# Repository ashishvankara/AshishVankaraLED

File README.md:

# Ashish Vankara Prototyping Skills: Blinking Light Project

## Introduction
An LED light-blinking apparatus that switches between 5 different operating modes (shown below) was created.

    - off
    - brightest
    - Intermediate Brightness
    - Least Bright
    - Flashing at 2Hz
 
## Design Repository Description
This design repository is organized into the following directories:

    -Docs: contains datasheets, and initial circuit and software planning schematics
    -Electronics: contains the initial circuit diagrams
    -Hardware: contains the project's ECAD files
        - Final iteration: LEDproject.11.18.18.brd & LEDproject.11.18.18.sch
    -Mechanical: contains the project's CAD files
        - Final iteration: Bottom.Final.STL & Top.Final.STL
    -Software: contains the software flow chart as well as the arduino script utilized in this project

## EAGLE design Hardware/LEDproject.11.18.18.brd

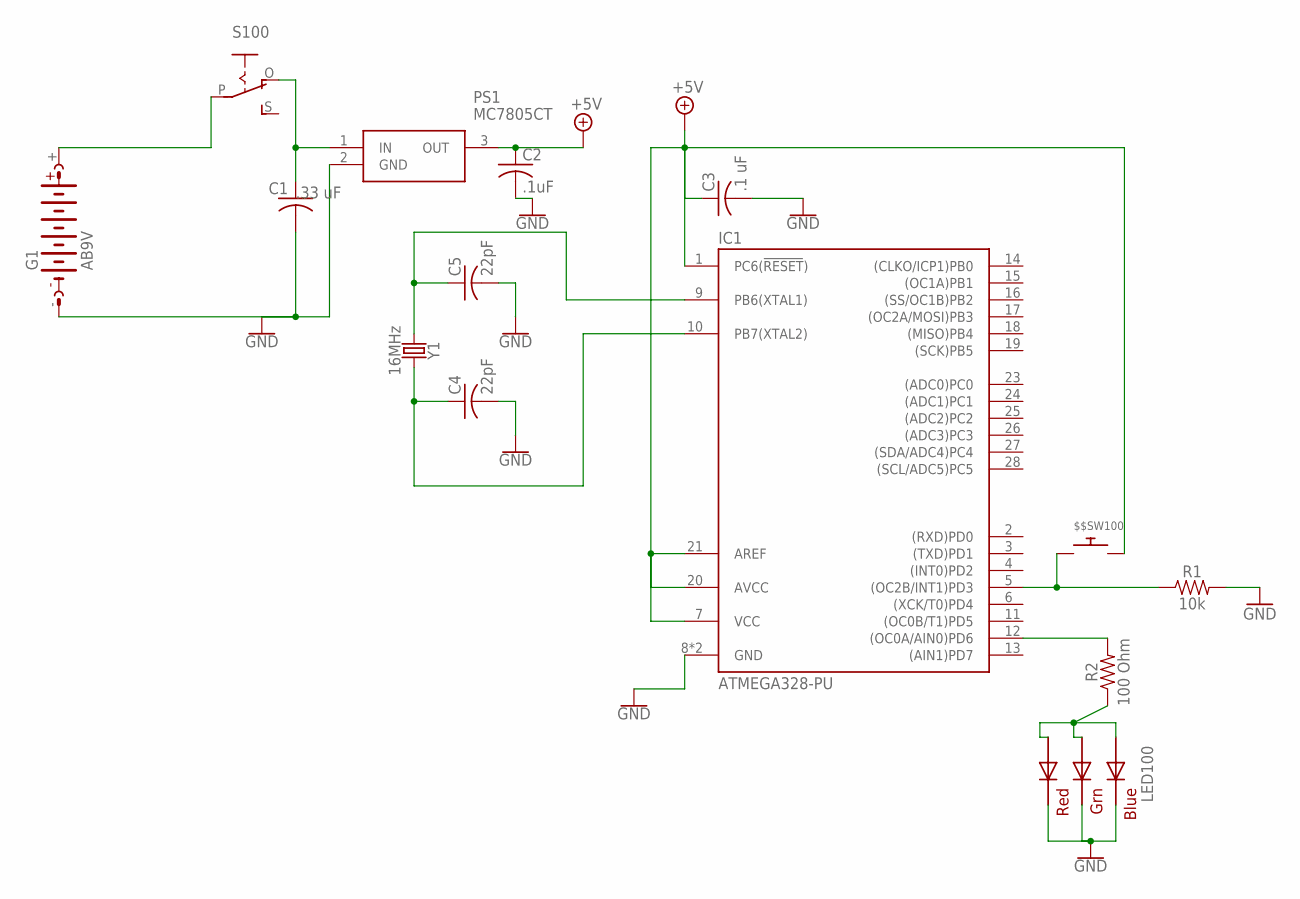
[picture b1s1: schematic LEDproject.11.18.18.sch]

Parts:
$$SW100: SWITCH_PUSHBUTTONEVQ-PE; TACT_PANA-EVQ
C1: C-US025-030X050; C025-030X050
C2: .1uF; C025-030X050
C3: .1 uF; C025-030X050
C4, C5: 22pF; C025-030X050
G1: AB9V
IC1: ATMEGA328-PU; DIL28
LED100: RGBLED5050
PS1: MC7805CT; TO254P482X997X1968-3P
R1: 10k; AXIAL-0.3
R2: 100 Ohm; AXIAL-0.3
S100: EG1218S; EG1218
Y1: 16MHz; HC49US

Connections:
+5V: $$SW100.P$2, C2.1, C3.1, IC1.1 (PC6(!RESET!)), IC1.7 (VCC), IC1.20 (AVCC), IC1.21 (AREF), PS1.3 (OUT)
GND: C1.2, C2.2, C3.2, C4.2, C5.2, G1.-, IC1.8 (GND), IC1.22 (GND), LED100.4 (BLUE_C), LED100.5 (RED_C), LED100.6 (GREEN_C), PS1.2 (GND), R1.P$2 (2)
unnamed: C5.1, IC1.9 (PB6(XTAL1)), Y1.1
unnamed: C4.1, IC1.10 (PB7(XTAL2)), Y1.2
unnamed: G1.+, S100.P
unnamed: LED100.1 (GREEN_A), LED100.2 (RED_A), LED100.3 (BLUE_A), R2.P$1 (1)
unnamed: C1.1, PS1.1 (IN), S100.O
unnamed: $$SW100.P$1, IC1.5 ((OC2B/INT1)PD3), R1.P$1 (1)
unnamed: IC1.12 ((OC0A/AIN0)PD6), R2.P$2 (2)

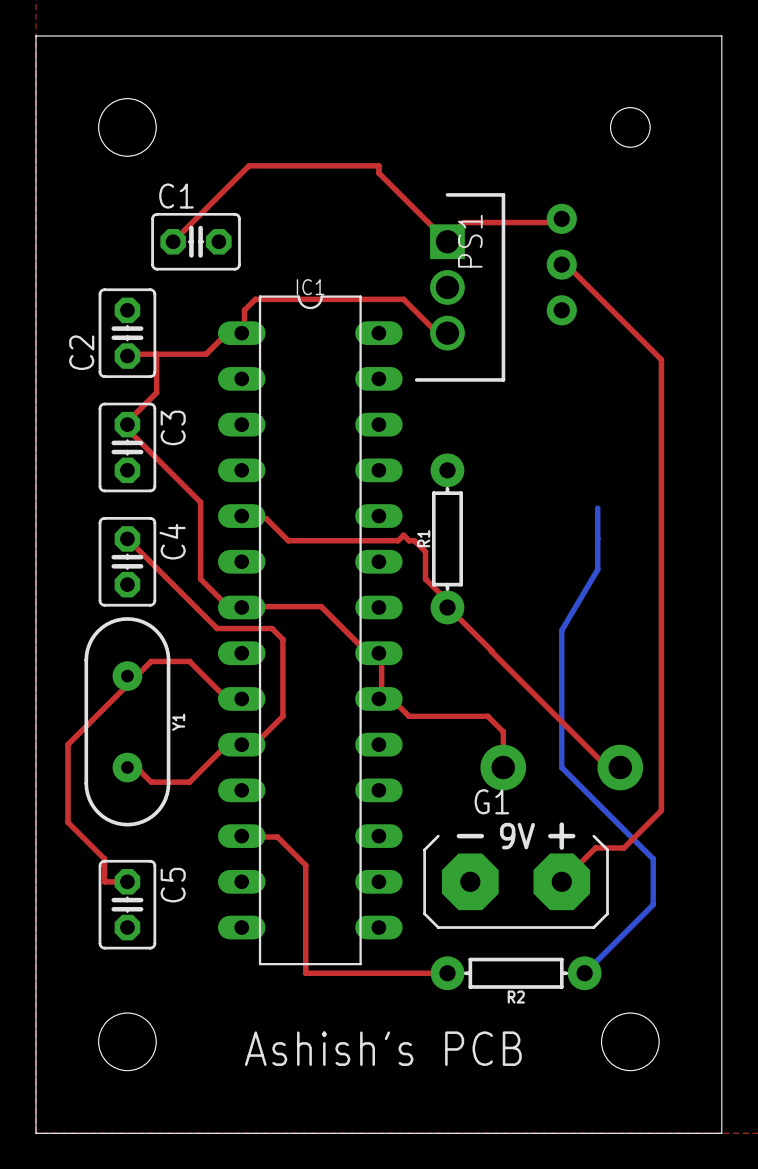
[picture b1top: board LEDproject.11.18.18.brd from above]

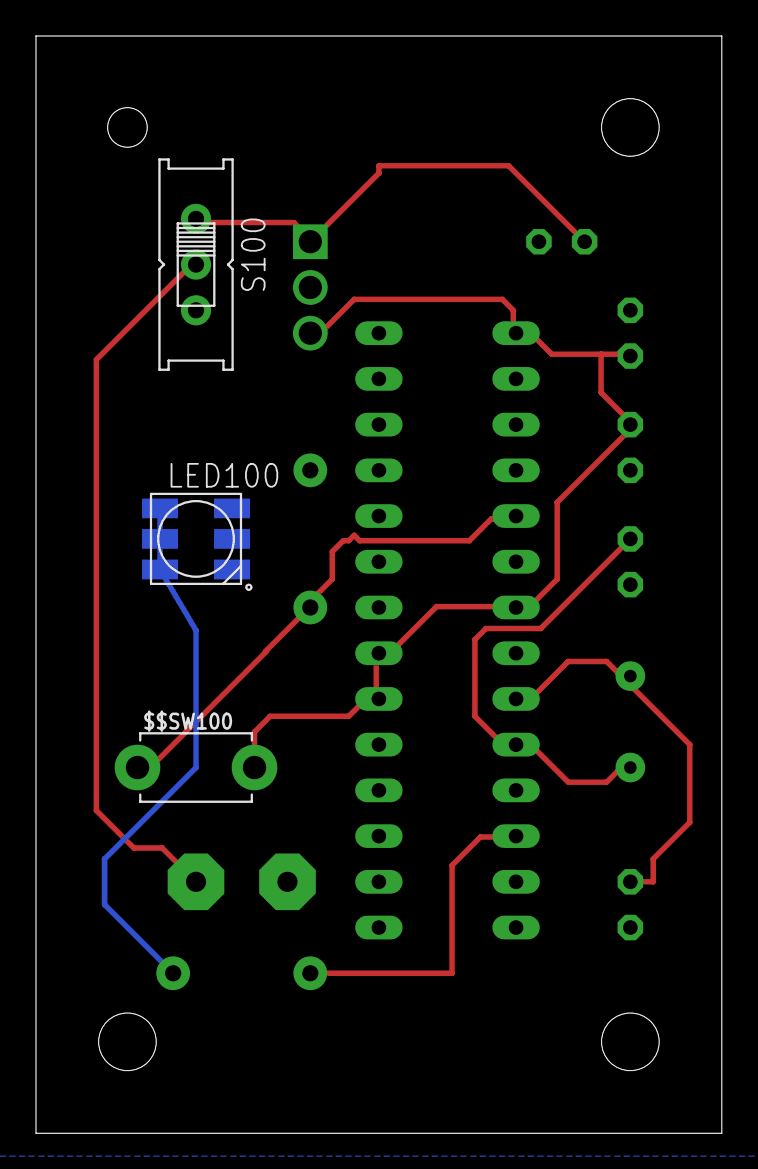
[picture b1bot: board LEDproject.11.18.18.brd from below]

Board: 2 copper layers, 38.1 x 61.0 mm, 14 parts (3 on the bottom side), 9 nets.

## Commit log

2018-10-15 test commit
2018-10-16 Initial block diagram and concept generation
2018-11-01 Milestone 3: Added Circuit Diagram + Arduino Script
2018-11-01 Forgot to work on a branch, silly me
2018-11-01 added flow chart; had unknowingly finished the code before doing the flowchart
2018-11-05 adjusted pin for PWM
2018-11-05 improved circuit diagram
2018-11-07 Updated software to include debouncing
2018-11-08 First iteration of PCB
2018-11-08 Added EAGLE files
2018-11-12 updated breadboard and circuit to match schematics
2018-11-15 Updated PCB
2018-11-18 Changed LED to be surface mount
2018-11-18 connected three anodes of LED together
2018-11-19 Adjusted PCB mounting hole, preliminary mechanical drawings
2018-11-27 added datasheet and created stl files
2018-12-02 modifications to pcb mounts and bolt for casing
2018-12-02 adjusted fillets for 3d printer resolution and made .stl
2018-12-02 increased debouncing time delay to 200ms
2018-12-05 adjusted bottom casing to make room for battery
2018-12-06 modified cut for push button
2018-12-12 Adjusted hold position in top casing

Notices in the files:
parts and their libraries:
SparkFun-Resistors: Licensing: Creative Commons ShareAlike 4.0 International - https://creativecommons.org/licenses/by-sa/4.0
